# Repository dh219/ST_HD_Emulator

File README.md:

# ATARI ACSI Hard Drive Controller Emulator
Use your ageing ATARI ST again!

KISS principal implemented throughout!

This has been done before. I don't pretend to have invented this. However, this design uses the Raspberry PI PICO, which, at time of designing, had not been done before.

This is in know way the finished article. I have uploaded to git simply because there is some interest, and who knows? maybe others will conribute to make a "complete" package.

### Initial Release:
Both PICO CPU cores are used. Core 2 is solely used for decoding command packets. Core 1, prints command data and live status. 

Note the shell... you can do things whilst the emulator is doing its stuff. At the moment, there isn't much. Just date, time reporting. But partition dumps could be performed, partitioning and formatting sd cards etc.

Revised Hardware design
The TXB0108 part is not suitable for this project. A 74xxx245 part is needed as I used in the prototype. Why oh why did I change it !!!

### Latest Improvements:
* Incorporated local spi and sdcard files and optimised for this project.
* Removed the No-OS-FatFS dependancy.
* Two SD-CARDS are now functional.
* Tested with ICD driver, HDDriver driver, AHDI driver, PPutnik driver.
* Tested with EmuTOS and FreeMint.
Typical transfer speeds are > 900 KB/s and peak just under 1100 KB/s. Dependent upon sd-card used.

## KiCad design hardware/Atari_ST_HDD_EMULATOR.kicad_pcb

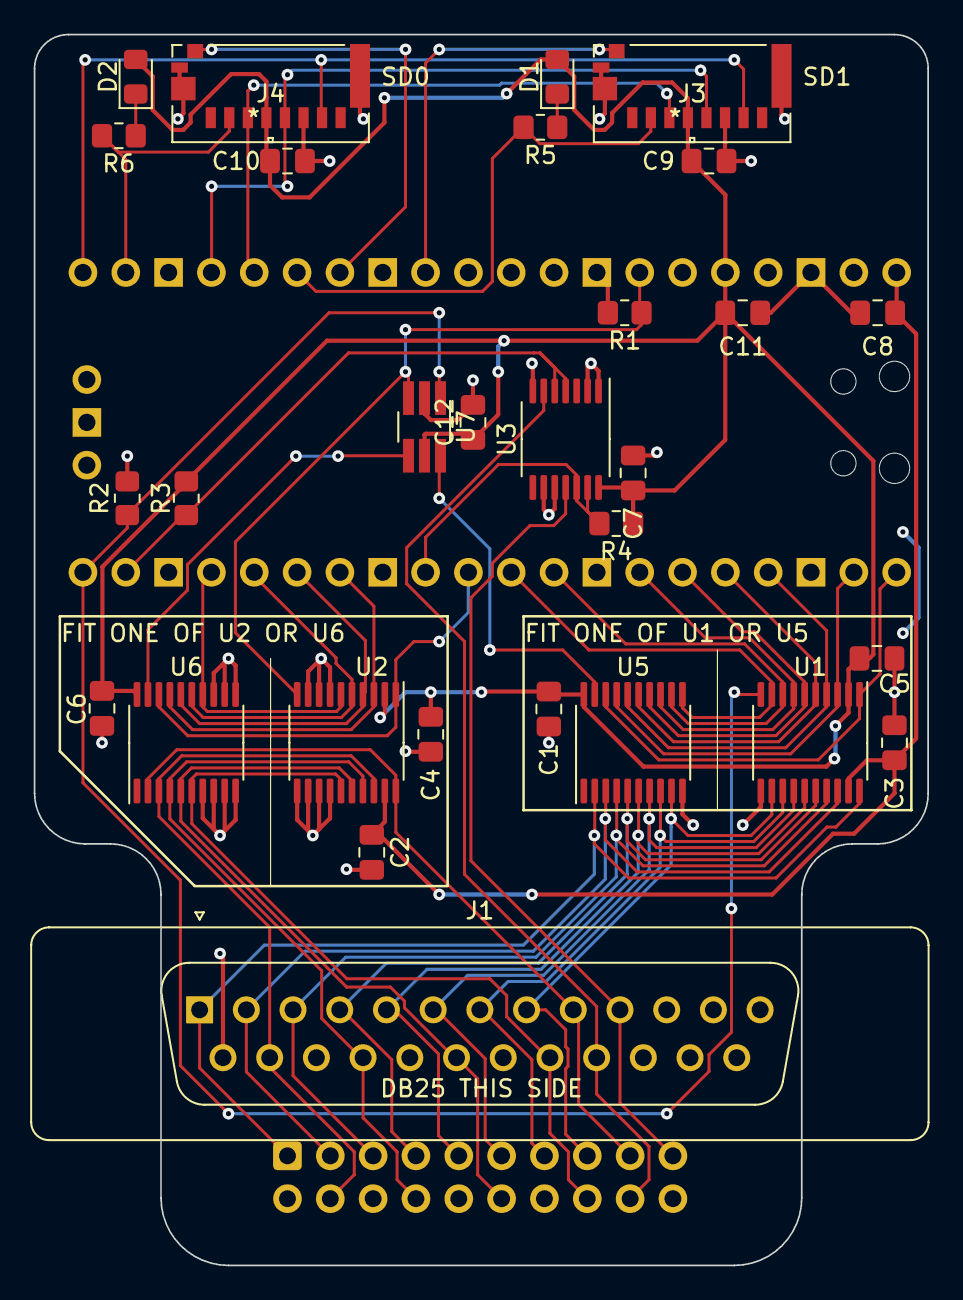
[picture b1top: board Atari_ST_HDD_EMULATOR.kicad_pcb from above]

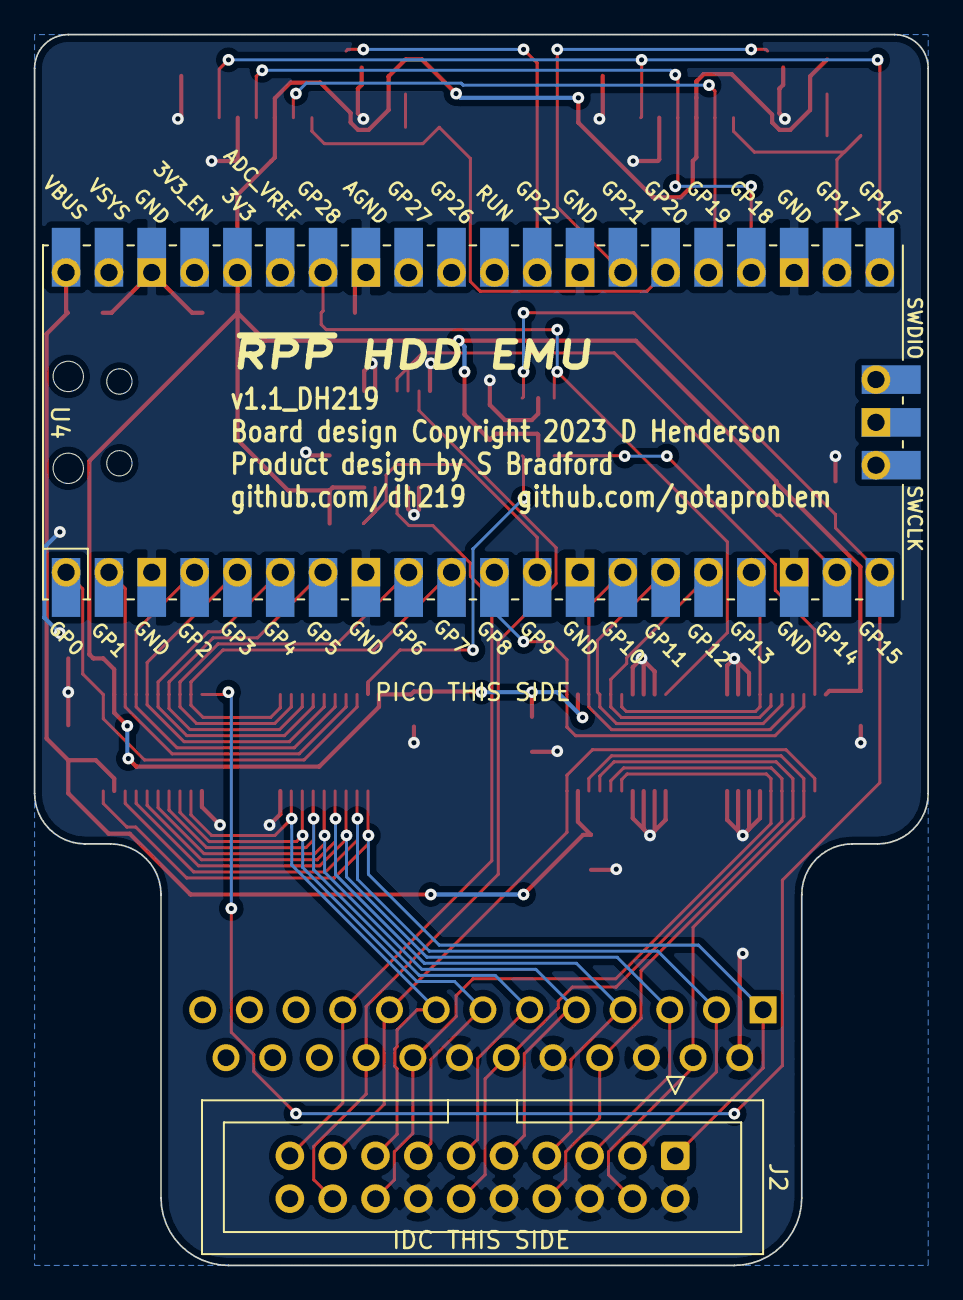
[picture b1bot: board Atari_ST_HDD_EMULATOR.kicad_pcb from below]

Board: 2 copper layers, 53.0 x 73.0 mm, 31 parts (2 on the bottom side), 46 nets.

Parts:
C1, C2, C3, C4, C5, C6, C7, C8, C11, C12: 100nF; C_0805_2012Metric_Pad1.18x1.45mm_HandSolder
C9, C10: 1nF; C_0805_2012Metric_Pad1.18x1.45mm_HandSolder
D1, D2: LED; LED_0805_2012Metric_Pad1.15x1.40mm_HandSolder
J1: DB25_Male; DSUB-25_Male_Vertical_P2.77x2.84mm
J2: IDC 20pin; IDC-Header_2x10_P2.54mm_Vertical
J3, J4: 473092285; molex_47309-2285_sdcard
R1, R2, R3, R4: R10K; R_0805_2012Metric_Pad1.20x1.40mm_HandSolder
R5, R6: R220; R_0805_2012Metric_Pad1.20x1.40mm_HandSolder
U1, U2: TXB0108PWR; TSSOP-20_4.4x6.5mm_P0.65mm
U3: 74HCT125PW; TSSOP-14_4.4x5mm_P0.65mm
U4: Pico; RPi_Pico_SMD_TH
U5, U6: SN74CB3T3245PWR; TSSOP-20_4.4x6.5mm_P0.65mm
U7: 74LVC2G04; TSOT-23-6_HandSoldering

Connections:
+3V3: C1.1, C4.1, C5.1, C6.1, C7.1, C9.1, C10.1, C11.1, C12.1, D1.2, D2.2, J3.P4, J4.P4, R3.1, R4.1, U1.2, U2.2, U3.14, U4.36, U5.20, U6.20, U7.5
+5V: C2.1, C3.1, C8.1, U1.19, U2.19, U4.40
/AD0: J1.1, J2.1, U1.20, U5.2
/AD1: J1.2, J2.3, U1.18, U5.3
/AD2: J1.3, J2.5, U1.17, U5.4
/AD3: J1.4, J2.7, U1.16, U5.5
/AD4: J1.5, J2.9, U1.15, U5.6
/D0: U1.1, U4.1, U5.18
/D1: U1.3, U4.2, U5.17
/D2: U1.4, U4.4, U5.16
/D3: U1.5, U4.5, U5.15
/D4: U1.6, U4.6, U5.14
/D5: U1.7, U4.7, U5.13
/D6: U1.8, U4.9, U5.12
/D7: U1.9, U4.10, U5.11
/~CNTRLBUSENABLE: U6.19, U7.4
/~DATABUSENABLE: U5.19, U7.6
A1: U2.5, U4.16, U6.15
AA1: J1.19, J2.12, U2.16, U6.5
AACK: J1.17, J2.8, U2.17, U6.4
ACK: U2.4, U4.15, U6.16
ACS: J1.9, J2.17, U2.20, U6.2
AD5: J1.6, J2.11, U1.14, U5.7
AD6: J1.7, J2.13, U1.13, U5.8
AD7: J1.8, J2.15, U1.12, U5.9
ADRQ: J1.22, J2.18, U3.6
AIRQ: J1.10, J2.19, U3.11
ARST: J1.15, J2.4, U2.18, U6.3
ARW: J1.21, J2.16, U2.15, U6.6
CD0: J4.G4, U4.27
CD1: J3.G4, U4.29
CNTRLBUSENABLE: R1.1, U2.10, U4.34, U7.3
CS: U2.1, U4.11, U6.18
CS0: J4.P2, R6.2, U4.22
CS1: J3.P2, R5.2, U4.26
DATABUSENABLE: R2.1, U1.10, U4.20, U7.1
DRQ: R3.2, U3.4, U3.5, U4.19
GND: C1.2, C2.2, C3.2, C4.2, C5.2, C6.2, C7.2, C8.2, C9.2, C10.2, C11.2, C12.2, J1.14, J1.16, J1.18, J1.20, J2.2, J2.6, J2.10, J2.14, J3.G1, J3.G2, J3.G3, J3.P6, J4.G1, J4.G2, J4.G3, J4.P6, R1.2, R2.2, U1.11, U2.7, U2.8, U2.9, U2.11, U2.12, U2.13, U2.14, U3.1, U3.2, U3.7, U3.9, U3.10, U4.3, U4.8, U4.13, U4.18, U4.23, U4.28, U4.33, U4.38, U5.10, U6.7, U6.8, U6.9, U6.10, U6.11, U6.12, U6.13, U7.2
IRQ: R4.2, U3.12, U3.13, U4.12
unnamed: D1.1, R5.1
unnamed: D2.1, R6.1
RST: U2.3, U4.14, U6.17
RW: U2.6, U4.17, U6.14
SPI_CLK: J3.P5, J4.P5, U4.24
SPI_RX: J3.P7, J4.P7, U4.21
SPI_TX: J3.P3, J4.P3, U4.25

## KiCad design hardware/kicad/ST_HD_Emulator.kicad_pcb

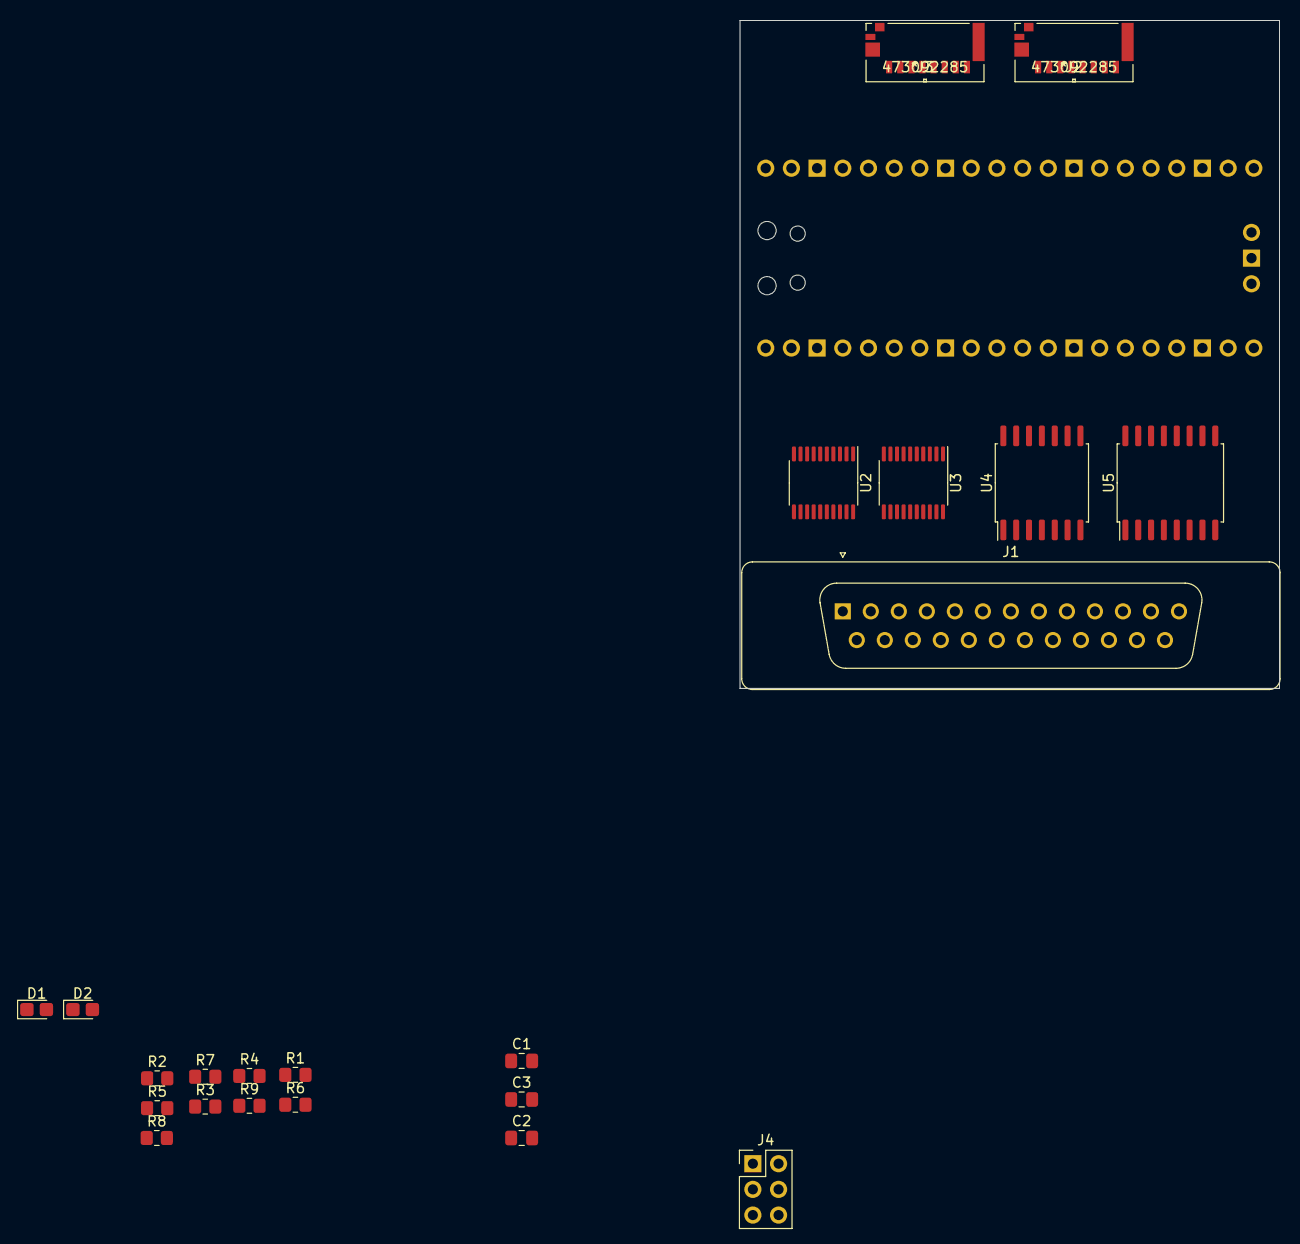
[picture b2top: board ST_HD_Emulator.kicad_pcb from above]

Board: 2 copper layers, 53.3 x 66.0 mm, 23 parts (1 on the bottom side), 49 nets, no tracks yet.

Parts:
C1, C2, C3: 100nF; C_0805_2012Metric_Pad1.18x1.45mm_HandSolder
D1, D2: LED; LED_0805_2012Metric_Castellated
J1: DB25_Male; DSUB-25_Male_Vertical_P2.77x2.84mm
J2, J3: 473092285; molex_47309-2285_sdcard
J4: Controller ID Select; PinHeader_2x03_P2.54mm_Vertical
R1, R2: R220; R_0805_2012Metric_Pad1.20x1.40mm_HandSolder
R3, R4, R8, R9: R1K; R_0805_2012Metric_Pad1.20x1.40mm_HandSolder
R5, R6, R7: R10K; R_0805_2012Metric_Pad1.20x1.40mm_HandSolder
U1: Pico; RPi_Pico_SMD_TH
U2, U3: TXB0108DQSR; TSSOP-20_4.4x6.5mm_P0.65mm
U4: 74LS125; SOIC-14W_7.5x9mm_P1.27mm
U5: 74LS85; SOIC-16W_7.5x10.3mm_P1.27mm

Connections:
+3V3: C2.1, C3.1, D1.2, D2.2, J2.P4, J3.P4, U1.36, U2.5, U3.5, U3.6
+5V: C1.1, R4.1, R8.1, R9.1, U1.40, U2.16, U3.16, U4.14, U5.16
/AD0: J1.1, U2.20
/AD1: J1.2, U2.19
/AD2: J1.3, U2.18
/AD3: J1.4, U2.17
/AD4: J1.5, U2.14
/D0: U1.1, U2.1
/D1: U1.2, U2.2
/D2: U1.4, U2.3
/D3: U1.5, U2.4
/D4: U1.6, U2.7
/D5: U1.7, U2.8
/D6: U1.9, U2.9
/D7: U1.10, U2.10
A1: U1.16, U3.4
AA1: J1.19, U3.17, U5.1
AACK: J1.17, U3.18
ACK: U1.15, U3.3
ACS: J1.9, U3.20, U5.15
AD5: J1.6, U2.13, U5.14
AD6: J1.7, U2.12, U5.11
AD7: J1.8, U2.11, U5.9
ARST: J1.15, U3.19
ARW: J1.21, U3.14
CD0: J3.G4, U1.27
CD1: J2.G4, U1.29
CONTROLLERID: U3.11, U5.6
CS: U1.11, U3.1
CS0: J3.P2, R1.2, U1.22
CS1: J2.P2, R2.2, U1.26
DATABUSENABLE: R3.1, U1.20, U2.6
DRQ: R8.2, U1.19, U4.4, U4.5
GND: C1.2, C2.2, C3.2, J1.14, J1.16, J1.18, J1.20, J2.G1, J2.G2, J2.G3, J2.P6, J3.G1, J3.G2, J3.G3, J3.P6, R3.2, R5.2, R6.2, R7.2, U1.3, U1.8, U1.13, U1.18, U1.23, U1.28, U1.33, U1.38, U1.42, U2.15, U3.15, U4.7, U5.8
IRQ: R9.2, U1.12, U4.1, U4.2
unnamed: D1.1, R1.1
unnamed: D2.1, R2.1
unnamed: J1.10, U4.3
unnamed: J1.22, U4.6
unnamed: J4.1, J4.3, J4.5, R4.2
unnamed: J4.2, R7.1, U5.13
unnamed: J4.4, R6.1, U5.12
unnamed: J4.6, R5.1, U5.10
RST: U1.14, U3.2
RW: U1.17, U3.7
SELECTED: U1.31, U3.10
SPI_CLK: J2.P5, J3.P5, U1.24
SPI_RX: J2.P7, J3.P7, U1.21
SPI_TX: J2.P3, J3.P3, U1.25

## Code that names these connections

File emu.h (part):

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#define CS                  8                   /* GPIO 08 input  */
#define IRQ                 9                   /* GPIO 09 output */
#define RST                 10                  /* GPIO 10 input  */
#define ACK                 11                  /* GPIO 11 input  */
#define A1                  12                  /* GPIO 12 input  */
#define RW                  13                  /* GPIO 13 input  - read active-high, write active-low */
#define DRQ                 14                  /* GPIO 14 output */
#define DATA_BUS_CNTRL      15                  /* GPIO 15 output - data bus control - low = high-impedance */
#define SPI_SDO             16                  /* GPIO 16 output - MISO */
#define MICROSD_CARD_CS0    17                  /* GPIO 17 output - microSD card socket 1 CS, active-low */
#define SPI_CLK             18                  /* GPIO 18 output - microSD SPI clock */
#define SPI_SDI             19                  /* GPIO 19 input  - MOSI */
#define MICROSD_CARD_CS1    20                  /* GPIO 20 output - microSD card socket 2 CS, active-low */
#define MICROSD_CARD_CD0    21                  /* GPIO 21 input  - microSD card socket 1 CD, active-low */
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#else
#define ONBOARD_LED         25                  /* GPIO 25 output - PI PICO onboard LED */
#endif
#define CONTROLLER_SELECT   26                  /* GPIO 26 input  - hardware controller ID match - high = selected */
#define RTC_ENABLED         27                  /* GPIO 27 input  - hardware jumper 5-6 ON = high = RTC enabled */
#define CONTROL_BUS_CNTRL   28                  /* GPIO 28 output - control bus enable */

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#define CS_MASK             (1 << CS)           /* 0x00000100 */
#define IRQ_MASK            (1 << IRQ)          /* 0x00000200 */
#define RST_MASK            (1 << RST)          /* 0x00000400 */ 
#define ACK_MASK            (1 << ACK)          /* 0x00000800 */ 
#define A1_MASK             (1 << A1)           /* 0x00001000 */ 
#define RW_MASK             (1 << RW)           /* 0x00002000 */ 
#define DRQ_MASK            (1 << DRQ)          /* 0x00004000 */ 

/* GPIO output masks - 32 bit values */
#define SPI_CS0_MASK        (1 << MICROSD_CARD_CS0) /* 0x00020000 */
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
#define IRQ_LO()            gpio_put (IRQ, LO);
#define IRQ_HI()            gpio_put (IRQ, HI);
#define DRQ_LO()            gpio_put (DRQ, LO);
#define DRQ_HI()            gpio_put (DRQ, HI);

#define dataBus(s)          gpio_put (DATA_BUS_CNTRL, !s)
#define newCMD()            gpio_get (A1) == LO && gpio_get (RW) == LO // future will be gpio_get (CONTROLLER_SELECT) == HI
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//#define waitCS()            while ( gpio_get ( CS ) == HI )
#define waitCS(s)           while ( gpio_get ( CS ) != s )
#define waitRW(s)           while ( gpio_get ( RW ) == s )
#define waitACK(s)          while ( gpio_get ( ACK ) == s )
#define waitRD()            while ( gpio_get ( RW ) == LO )
#define waitWR()            while ( gpio_get ( RW ) == HI )
#define waitA1()            while ( gpio_get ( A1 ) == LO )
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
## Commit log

2022-11-22 Started initial board layout
2022-12-05 First recorded segment done
2022-12-15 Changed schematic to reflect different pinout of PWR package on the TX0108. PCB design needs changing
2023-01-10 Started work on simplified version with alternative level shifters
2023-01-10 Initial tracing complete -- awaiting wiring of the IDC connector
2023-01-10 First draft of v1.0_dh219
2023-01-11 v1.0_dh219 as ordered -- mistake found in the SN74CB3T3245 logic, however.
2023-01-12 Fixing some issues with 1.0 => no logic inversion for the Texas chips & changing the 125 supply voltage to 3V3.
2023-06-06 Converted for building under Debian Stable
2023-06-07 Slow down startup to allow terminal to connect
2023-06-21 Reversed buffer polarity
2023-08-08 Hopefully working STE mods. Break the write down into chunks. Improved command handling.
2023-08-08 Adding binary uf2 of current build
2023-09-22 Working with ICD and HDDR8 under plain TOS on STE.
2023-09-22 Putting latest binary snap

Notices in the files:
hardware/Atari_ST_HDD_EMULATOR.kicad_pcb:
Copyright 2023 D Henderson based on a design by Steve Bradford
Board design Copyright 2023 D Henderson
parts and their libraries:
Copyright 2021 Accelerated Designs. All rights reserved.
